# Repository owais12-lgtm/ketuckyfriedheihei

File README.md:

# ketuckyfriedheihei

https://github.com/user-attachments/assets/ab107a92-7bb6-4f32-aefd-921b1ff62dd6

# about

This keyboard has 74 regular keys, 8 programmable macro keys, and 1 switch within the rotary encoder

# Images

# BOM

| Name | Purpose | Quantity | Total Cost (USD) | Link | Distributor |
|------|---------|----------|-----------------|------|-------------|
| PCB | PCB | 1 | $60.00 | [lioncircuits.com](https://www.lioncircuits.com/quote) | Lion Circuits |
| Keycaps | Keycaps | 1 | $30.00 | [curiositycaps.in](https://curiositycaps.in/products/polar-day-line-crack-side-backlit-cherry-keycaps) | Curiosity Caps |
| Akko V3 Silver | Switches | 2 | $32.00 | [stackskb.com](https://stackskb.com/store/akko-v3-silver-pro-switch-pack-of-45/) | StacksKB |
| OLED | OLED | 1 | $2.00 | [robu.in](https://robu.in/product/0-91-inch-128x32-i2c-iic-serial-blue-oled-lcd-display-module/) | Robu |
| Raspberry Pi Pico | MCU | 1 | $5.00 | [robu.in](https://robu.in/product/raspberry-pi-pico/) | Robu |

# CAD files

https://www.tinkercad.com/things/lyZ20fdyAEX-surprising-snicket

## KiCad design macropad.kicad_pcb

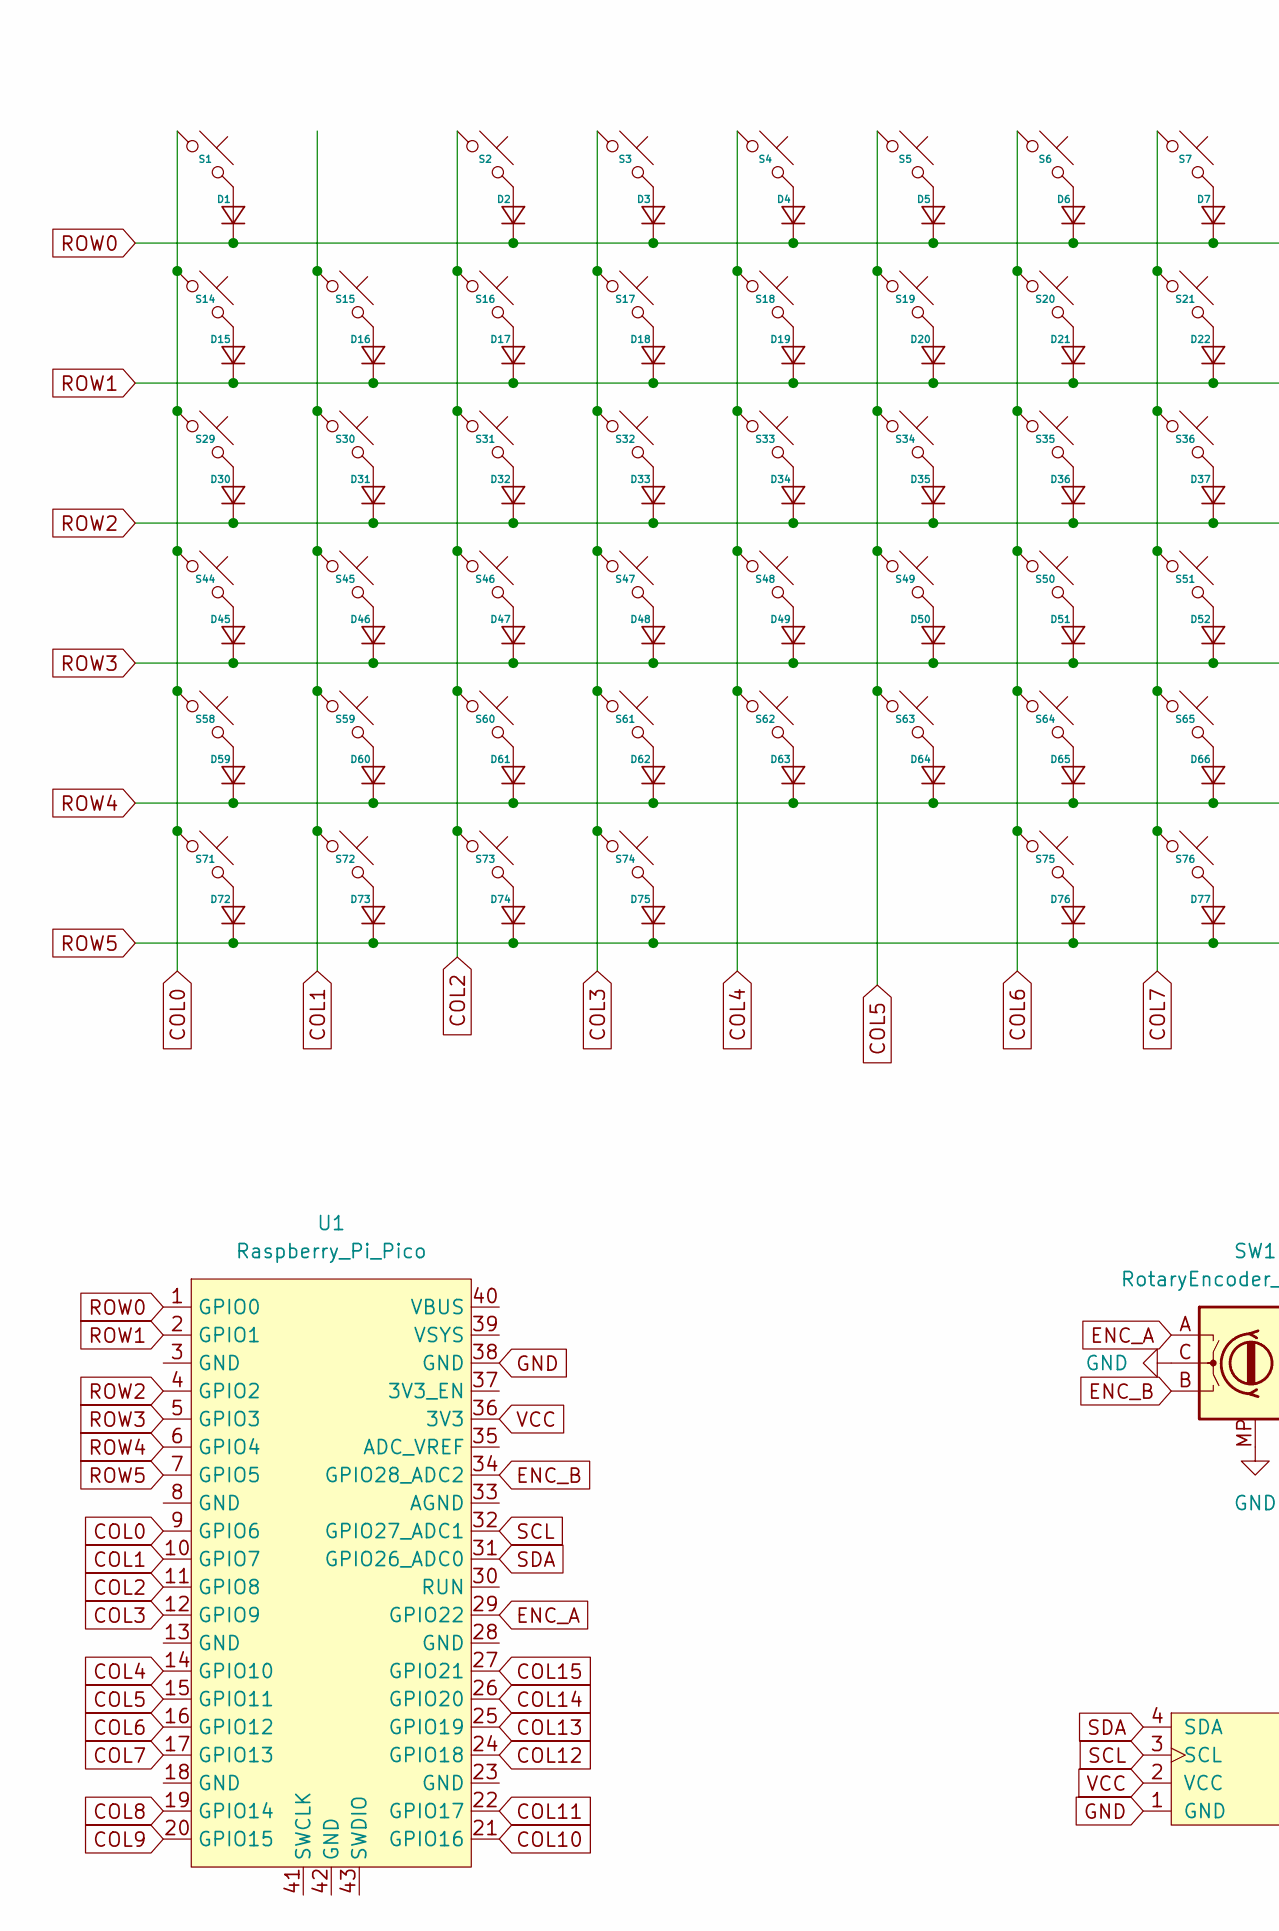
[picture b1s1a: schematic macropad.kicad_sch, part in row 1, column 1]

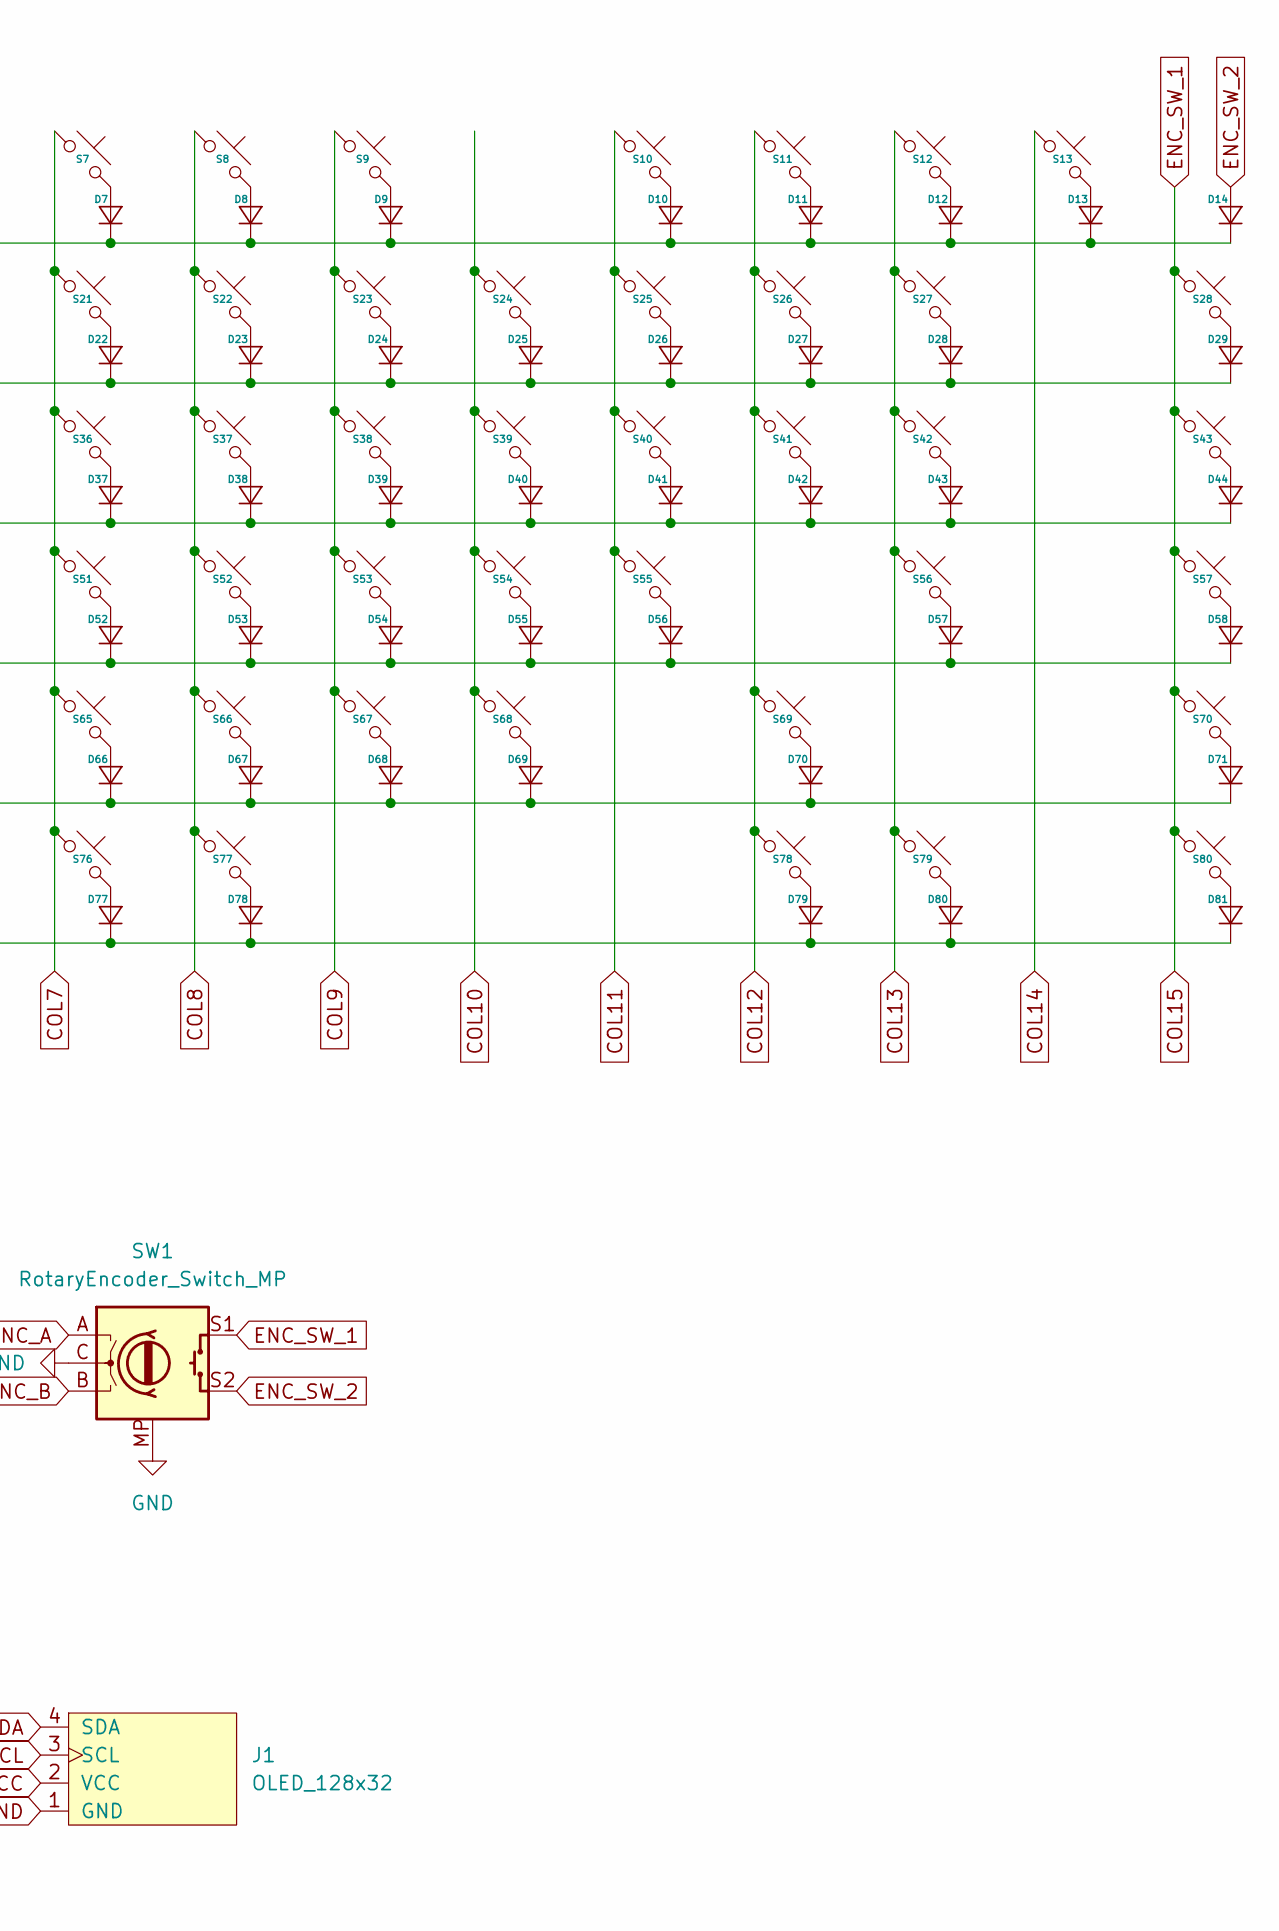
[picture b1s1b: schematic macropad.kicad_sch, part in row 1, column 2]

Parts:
D1, D2, D3, D4, D5, D6, D7, D8, D9, D10, D11, D12, D13, D14, D15, D16, D17, D18, D19, D20, D21, D22, D23, D24, D25, D26, D27, D28, D29, D30, D31, D32, D33, D34, D35, D36, D37, D38, D39, D40, D41, D42, D43, D44, D45, D46, D47, D48, D49, D50, D51, D52, D53, D54, D55, D56, D57, D58, D59, D60, D61, D62, D63, D64, D65, D66, D67, D68, D69, D70, D71, D72, D73, D74, D75, D76, D77, D78, D79, D80, D81: Diode_DO-35
J1: OLED_128x32
S1, S2, S3, S4, S5, S6, S7, S8, S9, S10, S11, S12, S13, S14, S15, S16, S17, S18, S19, S20, S21, S22, S23, S24, S25, S26, S27, S28, S29, S30, S31, S32, S33, S34, S35, S36, S37, S38, S39, S40, S41, S42, S43, S44, S45, S46, S47, S48, S49, S50, S51, S52, S53, S54, S55, S56, S57, S58, S59, S60, S61, S62, S63, S64, S65, S66, S67, S68, S69, S70, S71, S72, S73, S74, S75, S76, S77, S78, S79, S80: MX_PCB_1.00u
SW1: RotaryEncoder_Switch_MP; RotaryEncoder_Alps_EC11E-Switch_Vertical_H20mm_MountingHoles
U1: Raspberry_Pi_Pico

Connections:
COL0: S1.1, S14.1, S29.1, S44.1, S58.1, S71.1, U1.9 (GPIO6)
COL1: S15.1, S30.1, S45.1, S59.1, S72.1, U1.10 (GPIO7)
COL2: S2.1, S16.1, S31.1, S46.1, S60.1, S73.1, U1.11 (GPIO8)
COL3: S3.1, S17.1, S32.1, S47.1, S61.1, S74.1, U1.12 (GPIO9)
COL4: S4.1, S18.1, S33.1, S48.1, S62.1, U1.14 (GPIO10)
COL5: S5.1, S19.1, S34.1, S49.1, S63.1, U1.15 (GPIO11)
COL6: S6.1, S20.1, S35.1, S50.1, S64.1, S75.1, U1.16 (GPIO12)
COL7: S7.1, S21.1, S36.1, S51.1, S65.1, S76.1, U1.17 (GPIO13)
COL8: S8.1, S22.1, S37.1, S52.1, S66.1, S77.1, U1.19 (GPIO14)
COL9: S9.1, S23.1, S38.1, S53.1, S67.1, U1.20 (GPIO15)
COL10: S24.1, S39.1, S54.1, S68.1, U1.21 (GPIO16)
COL11: S10.1, S25.1, S40.1, S55.1, U1.22 (GPIO17)
COL12: S11.1, S26.1, S41.1, S69.1, S78.1, U1.24 (GPIO18)
COL13: S12.1, S27.1, S42.1, S56.1, S79.1, U1.25 (GPIO19)
COL14: S13.1, U1.26 (GPIO20)
COL15: S28.1, S43.1, S57.1, S70.1, S80.1, SW1.S1, U1.27 (GPIO21)
ENC_A: SW1.A, U1.29 (GPIO22)
ENC_B: SW1.B, U1.34 (GPIO28_ADC2)
ENC_SW_2: D14.2 (A), SW1.S2
GND: J1.1 (GND), SW1.C, SW1.MP, U1.38 (GND)
unnamed: D1.2 (A), S1.2
unnamed: D2.2 (A), S2.2
unnamed: D3.2 (A), S3.2
unnamed: D4.2 (A), S4.2
unnamed: D5.2 (A), S5.2
unnamed: D6.2 (A), S6.2
unnamed: D7.2 (A), S7.2
unnamed: D8.2 (A), S8.2
unnamed: D9.2 (A), S9.2
unnamed: D10.2 (A), S10.2
unnamed: D11.2 (A), S11.2
unnamed: D12.2 (A), S12.2
unnamed: D13.2 (A), S13.2
unnamed: D15.2 (A), S14.2
unnamed: D16.2 (A), S15.2
unnamed: D17.2 (A), S16.2
unnamed: D18.2 (A), S17.2
unnamed: D19.2 (A), S18.2
unnamed: D20.2 (A), S19.2
unnamed: D21.2 (A), S20.2
unnamed: D22.2 (A), S21.2
unnamed: D23.2 (A), S22.2
unnamed: D24.2 (A), S23.2
unnamed: D25.2 (A), S24.2
unnamed: D26.2 (A), S25.2
unnamed: D27.2 (A), S26.2
unnamed: D28.2 (A), S27.2
unnamed: D29.2 (A), S28.2
unnamed: D30.2 (A), S29.2
unnamed: D31.2 (A), S30.2
unnamed: D32.2 (A), S31.2
unnamed: D33.2 (A), S32.2
unnamed: D34.2 (A), S33.2
unnamed: D35.2 (A), S34.2
unnamed: D36.2 (A), S35.2
unnamed: D37.2 (A), S36.2
unnamed: D38.2 (A), S37.2
unnamed: D39.2 (A), S38.2
unnamed: D40.2 (A), S39.2
unnamed: D41.2 (A), S40.2
unnamed: D42.2 (A), S41.2
unnamed: D43.2 (A), S42.2
unnamed: D44.2 (A), S43.2
unnamed: D45.2 (A), S44.2
unnamed: D46.2 (A), S45.2
unnamed: D47.2 (A), S46.2
unnamed: D48.2 (A), S47.2
unnamed: D49.2 (A), S48.2
unnamed: D50.2 (A), S49.2
unnamed: D51.2 (A), S50.2
unnamed: D52.2 (A), S51.2
unnamed: D53.2 (A), S52.2
unnamed: D54.2 (A), S53.2
unnamed: D55.2 (A), S54.2
unnamed: D56.2 (A), S55.2
unnamed: D57.2 (A), S56.2
unnamed: D58.2 (A), S57.2
unnamed: D59.2 (A), S58.2
unnamed: D60.2 (A), S59.2
unnamed: D61.2 (A), S60.2
unnamed: D62.2 (A), S61.2
unnamed: D63.2 (A), S62.2
unnamed: D64.2 (A), S63.2
unnamed: D65.2 (A), S64.2
unnamed: D66.2 (A), S65.2
unnamed: D67.2 (A), S66.2
unnamed: D68.2 (A), S67.2
unnamed: D69.2 (A), S68.2
unnamed: D70.2 (A), S69.2
unnamed: D71.2 (A), S70.2
unnamed: D72.2 (A), S71.2
unnamed: D73.2 (A), S72.2
unnamed: D74.2 (A), S73.2
unnamed: D75.2 (A), S74.2
unnamed: D76.2 (A), S75.2
unnamed: D77.2 (A), S76.2
unnamed: D78.2 (A), S77.2
unnamed: D79.2 (A), S78.2
unnamed: D80.2 (A), S79.2
unnamed: D81.2 (A), S80.2
ROW0: D1.1 (K), D2.1 (K), D3.1 (K), D4.1 (K), D5.1 (K), D6.1 (K), D7.1 (K), D8.1 (K), D9.1 (K), D10.1 (K), D11.1 (K), D12.1 (K), D13.1 (K), D14.1 (K), U1.1 (GPIO0)
ROW1: D15.1 (K), D16.1 (K), D17.1 (K), D18.1 (K), D19.1 (K), D20.1 (K), D21.1 (K), D22.1 (K), D23.1 (K), D24.1 (K), D25.1 (K), D26.1 (K), D27.1 (K), D28.1 (K), D29.1 (K), U1.2 (GPIO1)
ROW2: D30.1 (K), D31.1 (K), D32.1 (K), D33.1 (K), D34.1 (K), D35.1 (K), D36.1 (K), D37.1 (K), D38.1 (K), D39.1 (K), D40.1 (K), D41.1 (K), D42.1 (K), D43.1 (K), D44.1 (K), U1.4 (GPIO2)
ROW3: D45.1 (K), D46.1 (K), D47.1 (K), D48.1 (K), D49.1 (K), D50.1 (K), D51.1 (K), D52.1 (K), D53.1 (K), D54.1 (K), D55.1 (K), D56.1 (K), D57.1 (K), D58.1 (K), U1.5 (GPIO3)
ROW4: D59.1 (K), D60.1 (K), D61.1 (K), D62.1 (K), D63.1 (K), D64.1 (K), D65.1 (K), D66.1 (K), D67.1 (K), D68.1 (K), D69.1 (K), D70.1 (K), D71.1 (K), U1.6 (GPIO4)
ROW5: D72.1 (K), D73.1 (K), D74.1 (K), D75.1 (K), D76.1 (K), D77.1 (K), D78.1 (K), D79.1 (K), D80.1 (K), D81.1 (K), U1.7 (GPIO5)
SCL: J1.3 (SCL), U1.32 (GPIO27_ADC1)
SDA: J1.4 (SDA), U1.31 (GPIO26_ADC0)
VCC: J1.2 (VCC), U1.36 (3V3)

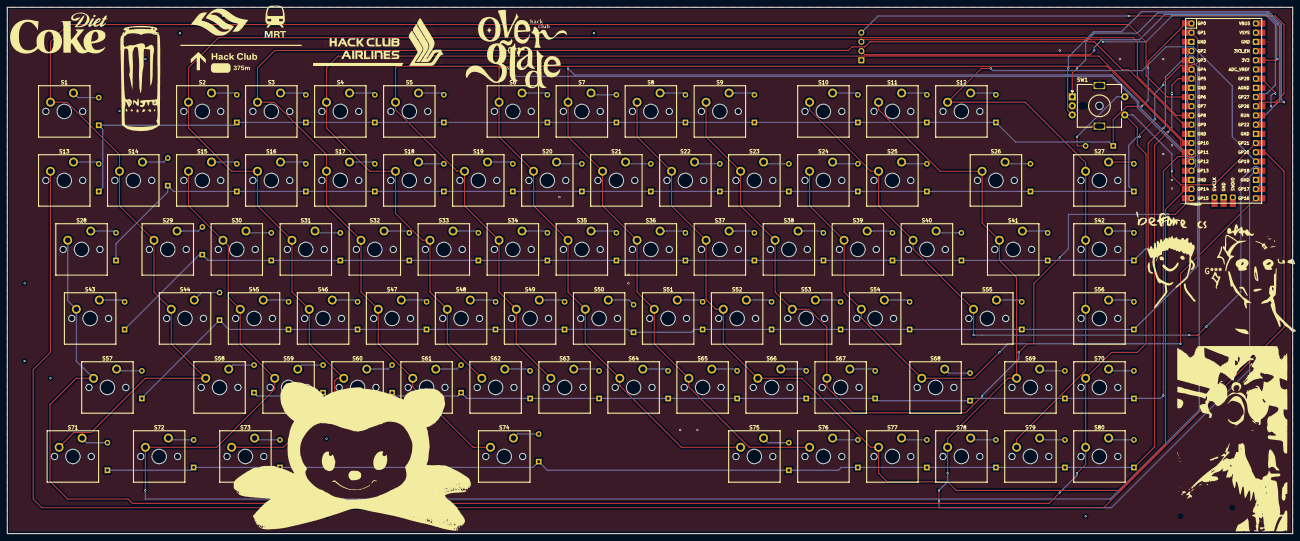
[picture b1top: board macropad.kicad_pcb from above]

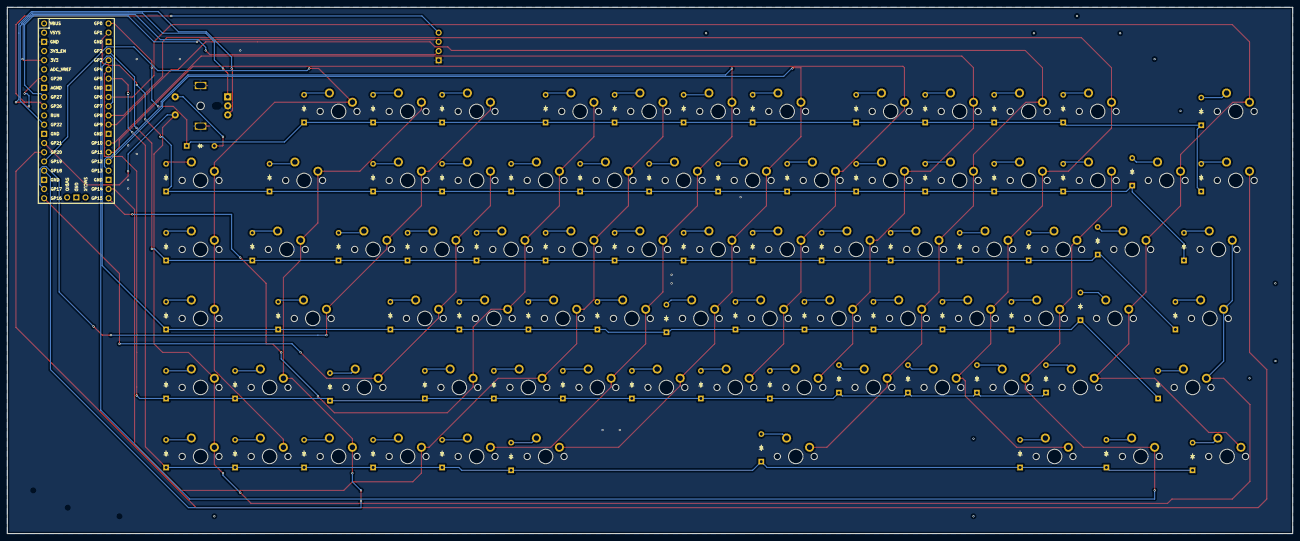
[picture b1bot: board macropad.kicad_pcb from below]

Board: 2 copper layers, 354.8 x 145.3 mm, 164 parts (81 on the bottom side), 109 nets.

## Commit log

2026-03-22 Create 1
